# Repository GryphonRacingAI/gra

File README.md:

# Development

## MacOS
On Mac, you may need to run `sudo chown -R $(whoami) ~/.docker` to allow docker to run without sudo.

## X11 auth
To enable X11 forwarding, run `xhost +local:docker` on host computer

## Pre-requisites
- $(hostname).local is broadcasted on the network via mDNS, for both bot and dev computer
- Docker needs to be run on linux

## Notes
- Please make sure the permissions are correct before committing
- To limit Gazebo CPU usage, decrease the update rate in the .world file
    ``` <real_time_update_rate>1000</real_time_update_rate> ```
    e.g. 1000 -> 250

## Known issues
- Ubuntu: memory leak (the memory mysteriously gets full). Deleting the forwarded ports solves the problem some of the time.
- Windows: git on Windows might change the line endings to CRLF which causes a problem when you build the repo. Make sure your line endings are LF if you get the `/bin/sh: 1: /usr/local/bin/apt-get-wrapper.sh: not found` error. `git config --global core.autocrlf false` and recloning the repo should solve the problem. You will need to modify the git config manually if you are using Github desktop and don't have git installed as a command line tool.

## Autonomous System Launch Sequence (full-scale ADS-DV model, with absolute odometry, autocross mission)
1) `roscore`
2) `roslaunch ackermann_vehicle_description ads_dv_sim.launch`
3) `roslaunch ultralytics_ros tracker_with_cloud.launch`
4) `roslaunch ultralytics_ros cone_mapper.launch`
5) `roslaunch fsai_mission autocross.launch`

## Do the following to disable GPU Acceleration: (refer to the wiki page)
1) Go to gra/.devcontainer/docker-compose.yml and comment the deploy section, then rebuild the Docker image in VScode
2) Go to gra/ros/cone_detection/launch/tracker_with_cloud.launch Comment line 17 and uncomment line 15
3) This step reduces Gazebo CPU usage by scaling the simulation time. The simulator will appear slower but CPU load will be reduced significantly.\
Go to gra/ros/ackermann_vehicle_gazebo/worlds/gazebo_world_building/track_small_features.world\
Line 76: <real_time_update_rate>700</real_time_update_rate>\
Reduce the value to reduce CPU load. 1000 is the default value where the simulation time unit = real time unit. When the value is 500, 1 simulation second = 2 real time second.\
Start with 700 and reduce gradually if the cone recognition process is unable to stablise. Unstable process can be observed by the cones swerving in Rviz when the car is steering.

## Commonly used commands
### Basic ROS
- `roscore` to launch ros
- `rosrun {package name} {node name}`
- `roslaunch {package name} {launch file}`
- `rostopic list`
- `rostopic echo {topic name}` print out messages to topic
### Sensors
- `roslaunch rplidar_ros rplidar_a1.launch` to launch the RPlidar
- `roslaunch realsense2_camera rs_aligned_depth.launch` to turn on the Intel depth camera
### Other
- `roslaunch gra_recording record.launch output_name:=recording1 duration:=10s` to record 10s of data
- `rosbag play -l recordings/recording1__timestamp.bag` to play a recording in a loop
- `rosbag record -o {name} --duration=30 /joint_states /rosout /rosout_agg /tf /tf_static /camera/aligned_depth_to_color/camera_info /camera/aligned_depth_to_color/image_raw/compressedDepth /camera/color/camera_info /camera/color/image_raw/compressed` includes the essential topics for recording depth camera rosbags.
- `roslaunch urdf_tutorial display.launch model:=ros/ackermann_vehicle_description/urdf/em_3905_hokuyo.urdf.xacro` to launch RViz with a basic setup (remember the X11 command above)
- `roslaunch gra_recording rviz.launch` to display a recorded stream in RViz
- `rosrun robot_upstart install fsai_api/launch/ads_dv_start.launch --job gra_supervisor_ros --symlink` to make ROS start automatically on boot
- `sudo cp ./driverless_startup.service /etc/systemd/system/driverless_startup.service && sudo systemctl daemon-reload && sudo systemctl enable driverless_startup.service` to register the startup service
- `gsettings set org.gnome.SessionManager logout-prompt false` to disable the 60s shutdown timer on Ubuntu (turn off immediately)

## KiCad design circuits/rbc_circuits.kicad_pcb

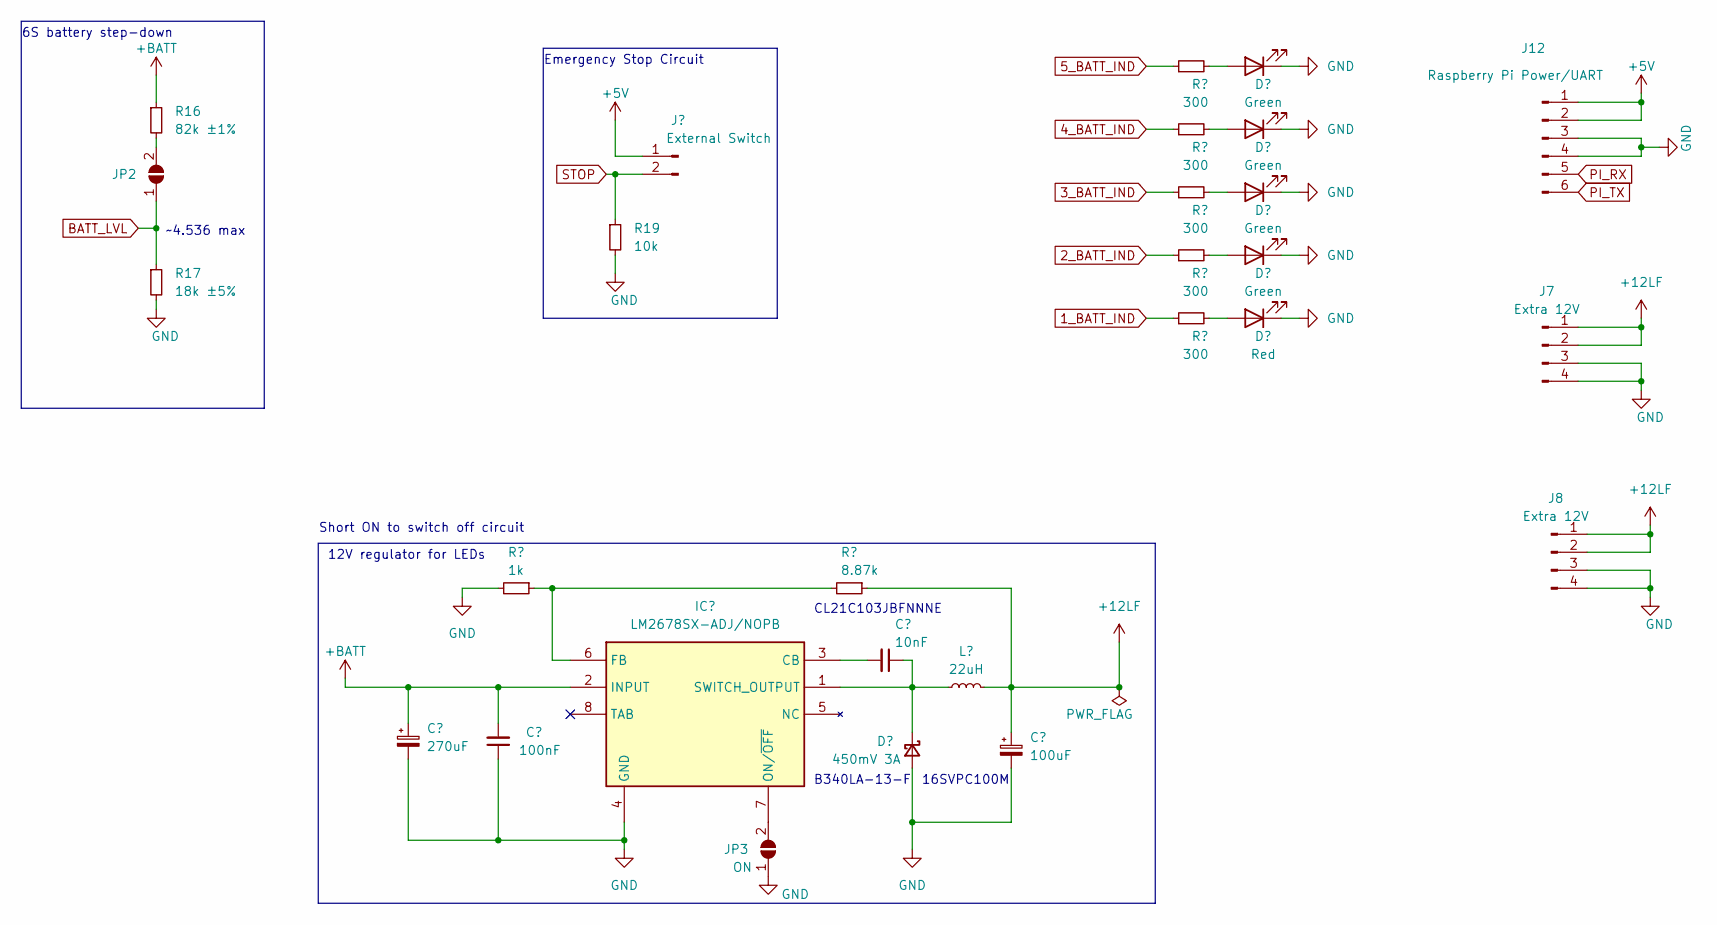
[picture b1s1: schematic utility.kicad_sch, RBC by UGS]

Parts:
C24: 270uF; EEHZS1H221P
C25: 100nF; C_0402_1005Metric
C26: 10nF; C_0805_2012Metric
C27: 100uF; 16SVF180M
D5: 450mV 3A; D_SMA
D6: Green; D_0805_2012Metric; Part No. 17-21/GHC-XS1T2M/3T
D7, D8, D9: Green; D_0805_2012Metric
D10: Red; D_0805_2012Metric; Part No. 17-215/R6C-AQ1R2B/3T
IC5: LM2678SX-ADJ/NOPB; KTW0007B_custom; Mouser Part Number 926-LM2678SX50NOPB
J5: External Switch; TerminalBlock_Phoenix_MKDS-3-2-5.08_1x02_P5.08mm_Horizontal
J7, J8: Extra 12V; Molex_Micro-Fit_3.0_43045-0412_2x02_P3.00mm_Vertical
J12: Raspberry Pi Power/UART; Molex_Micro-Fit_3.0_43045-0612_2x03_P3.00mm_Vertical
JP2: SolderJumper_2_Open; SolderJumper-2_P1.3mm_Open_RoundedPad1.0x1.5mm
JP3: ON; SolderJumper-2_P1.3mm_Open_RoundedPad1.0x1.5mm
L6: 22uH; INDPM110100X400N
R16: 82k ±1%; R_0603_1608Metric_Pad0.98x0.95mm_HandSolder; Part No. RTT038202FTP
R17: 18k ±5%; R_0603_1608Metric_Pad0.98x0.95mm_HandSolder
R18: 1k; R_0201_0603Metric
R19: 10k; R_0402_1005Metric
R20: 8.87k; R_0603_1608Metric
R21, R22, R23, R24, R25: 300; R_0603_1608Metric_Pad0.98x0.95mm_HandSolder

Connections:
1_BATT_IND: R25.1; also elsewhere on the board
2_BATT_IND: R24.1; also elsewhere on the board
3_BATT_IND: R23.1; also elsewhere on the board
4_BATT_IND: R22.1; also elsewhere on the board
5_BATT_IND: R21.1; also elsewhere on the board
+5V: J5.1; also elsewhere on the board
+12LF: C27.1, J7.1, J7.2, J8.1, J8.2, L6.2, R20.1
+BATT: C24.1, C25.2, IC5.2 (INPUT), R16.1; also elsewhere on the board
BATT_LVL: JP2.1 (A), R17.1; also elsewhere on the board
GND: C24.2, C25.1, C27.2, D5.2 (A), D6.1 (K), D7.1 (K), D8.1 (K), D9.1 (K), D10.1 (K), IC5.4 (GND), J7.3, J7.4, J8.3, J8.4, JP3.1 (A), R17.2, R18.2, R19.2; also elsewhere on the board
unnamed: C26.1, D5.1 (K), IC5.1 (SWITCH_OUTPUT), L6.1
unnamed: D6.2 (A), R21.2
unnamed: D7.2 (A), R22.2
unnamed: D8.2 (A), R23.2
unnamed: D9.2 (A), R24.2
unnamed: D10.2 (A), R25.2
unnamed: C26.2, IC5.3 (CB)
unnamed: IC5.6 (FB), R18.1, R20.2
unnamed: IC5.7 (ON/~OFF), JP3.2 (B)
unnamed: JP2.2 (B), R16.2
STOP: J5.2, R19.1; also elsewhere on the board

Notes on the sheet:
~4.536 max
6S battery step-down
16SVPC100M
12V regulator for LEDs
Short ON to switch off circuit
Emergency Stop Circuit
CL21C103JBFNNNE
B340LA-13-F

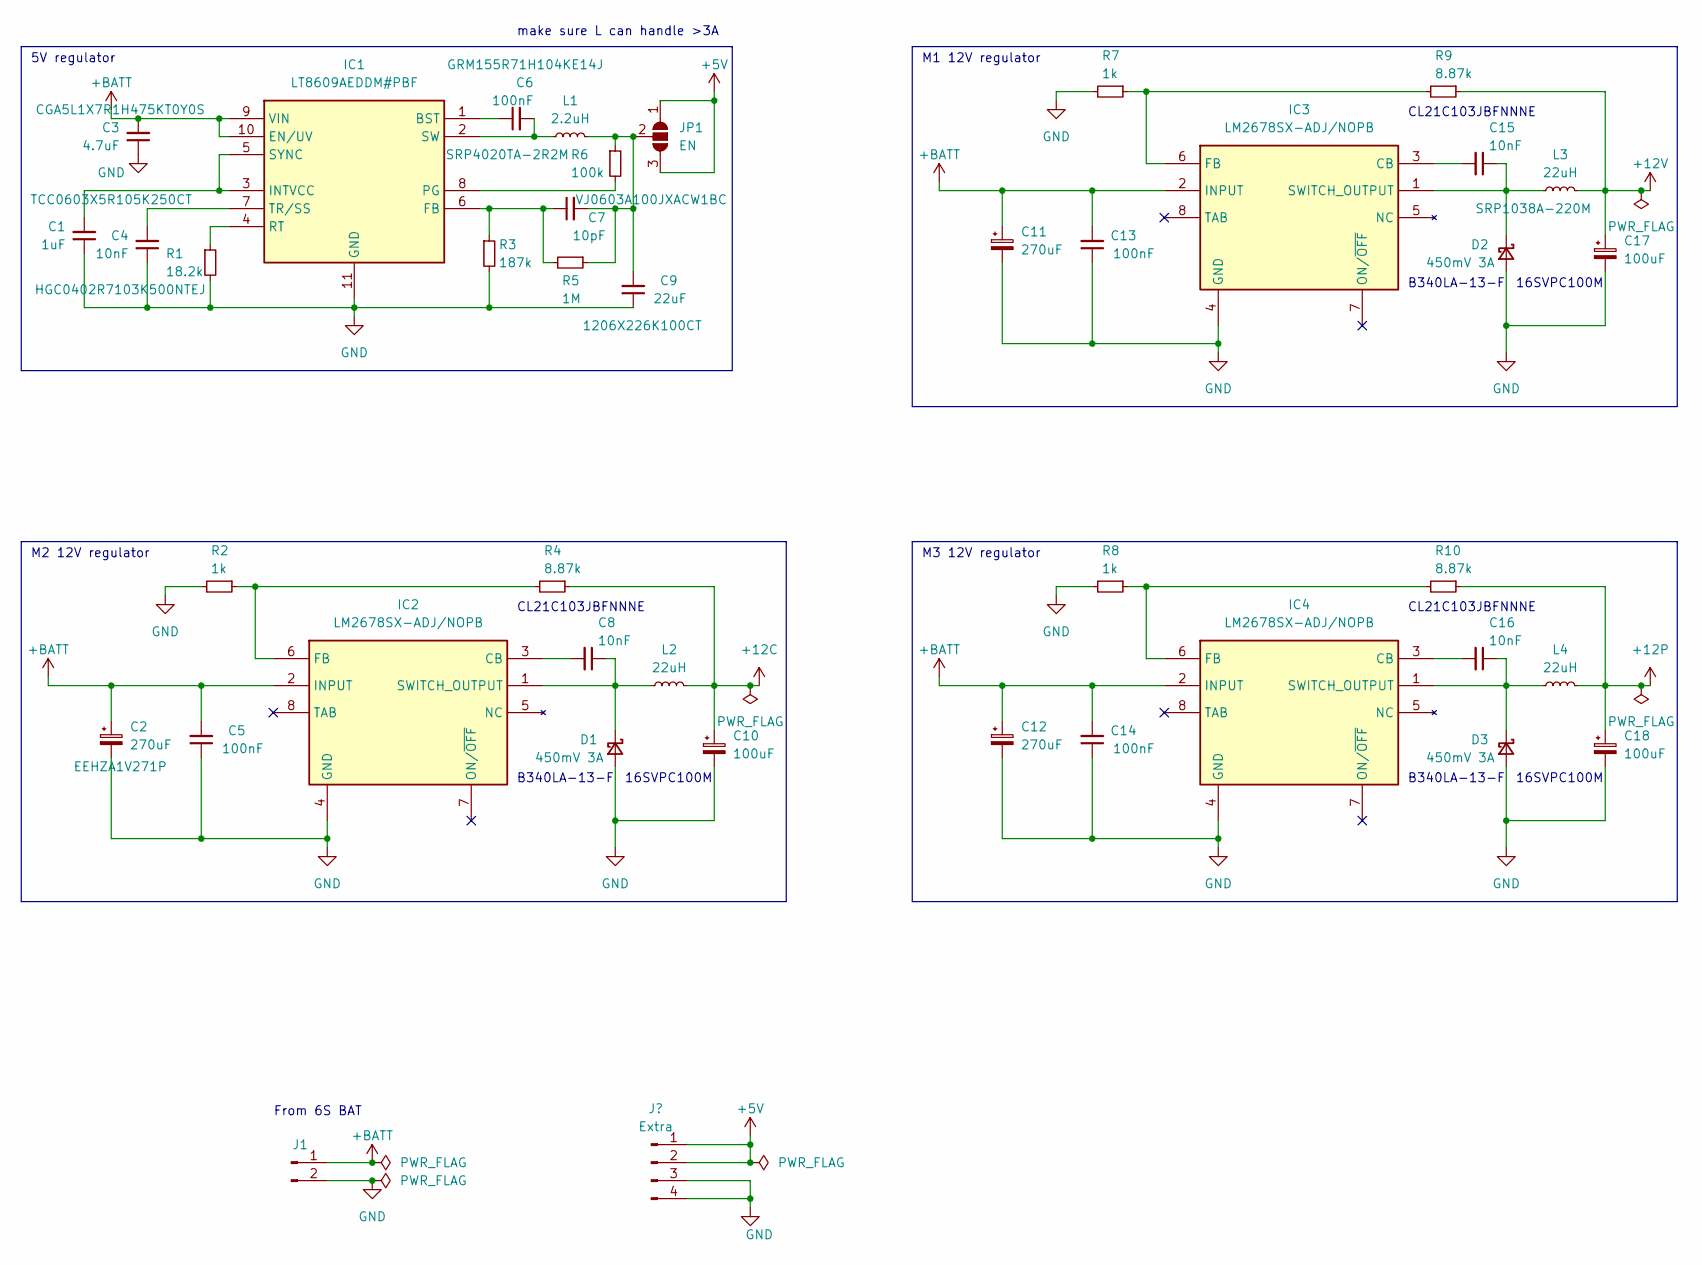
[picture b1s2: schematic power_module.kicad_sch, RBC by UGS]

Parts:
C1: 1uF; C_0603_1608Metric; Part No. TCC0603X5R105K250CT
C2: 270uF; EEHZS1H221P; Part No. EEHZA1V271P
C3: 4.7uF; C_1206_3216Metric; Part No. CGA5L1X7R1H475KT0Y0S
C4: 10nF; C_0402_1005Metric; Part No. HGC0402R7103K500NTEJ
C5, C13, C14: 100nF; C_0402_1005Metric
C6: 100nF; C_0402_1005Metric; Part No. GRM155R71H104KE14J
C7: 10pF; C_0603_1608Metric; Part No. VJ0603A100JXACW1BC
C8, C15, C16: 10nF; C_0805_2012Metric
C9: 22uF; C_1206_3216Metric; Part No. 1206X226K100CT
C10, C17, C18: 100uF; 16SVF180M
C11, C12: 270uF; EEHZS1H221P
D1, D2, D3: 450mV 3A; D_SMA
IC1: LT8609AEDDM#PBF; SON50P300X300X80-11N-D; Mouser Part Number 584-LT8609AEDDM#PBF
IC2, IC3, IC4: LM2678SX-ADJ/NOPB; KTW0007B_custom; Mouser Part Number 926-LM2678SX50NOPB
J1: Conn_01x02_Pin; TerminalBlock_Phoenix_MKDS-3-2-5.08_1x02_P5.08mm_Horizontal
J2: Extra; PinHeader_2x02_P2.54mm_Vertical
JP1: EN; SolderJumper-3_P2.0mm_Open_TrianglePad1.0x1.5mm
L1: 2.2uH; INDC4441X200N; Part No. SRP4020TA-2R2M
L2, L4: 22uH; INDPM110100X400N
L3: 22uH; INDPM110100X400N; Part No. SRP1038A-220M
R1: 18.2k; R_0603_1608Metric_Pad0.98x0.95mm_HandSolder; Part No. CRCW060318K2FKEA
R2: 1k; R_0201_0603Metric; Part No. RC0201FR-071KL
R3: 187k; R_0603_1608Metric; Part No. AC0603FR-07187KL
R4: 8.87k; R_0603_1608Metric; Part No. RT0603BRE078K87L
R5: 1M; R_0402_1005Metric; Part No. AC0402FR-071ML
R6: 100k; R_0201_0603Metric
R7, R8: 1k; R_0201_0603Metric
R9, R10: 8.87k; R_0603_1608Metric

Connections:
+5V: J2.1, J2.2, JP1.1 (A), JP1.3 (B); also elsewhere on the board
+12C: C10.1, L2.2, R4.1; also elsewhere on the board
+12P: C18.1, L4.2, R10.1; also elsewhere on the board
+12V: C17.1, L3.2, R9.1; also elsewhere on the board
+BATT: C2.1, C3.2, C5.2, C11.1, C12.1, C13.2, C14.2, IC1.9 (VIN), IC1.10 (EN/UV), IC2.2 (INPUT), IC3.2 (INPUT), IC4.2 (INPUT), J1.1; also elsewhere on the board
GND: C1.1, C2.2, C3.1, C4.1, C5.1, C9.1, C10.2, C11.2, C12.2, C13.1, C14.1, C17.2, C18.2, D1.2 (A), D2.2 (A), D3.2 (A), IC1.11 (GND), IC2.4 (GND), IC3.4 (GND), IC4.4 (GND), J1.2, J2.3, J2.4, R1.2, R2.2, R3.2, R7.2, R8.2; also elsewhere on the board
unnamed: C8.1, D1.1 (K), IC2.1 (SWITCH_OUTPUT), L2.1
unnamed: C15.1, D2.1 (K), IC3.1 (SWITCH_OUTPUT), L3.1
unnamed: C16.1, D3.1 (K), IC4.1 (SWITCH_OUTPUT), L4.1
unnamed: C6.1, IC1.1 (BST)
unnamed: C7.1, IC1.6 (FB), R3.1, R5.2
unnamed: C1.2, IC1.3 (INTVCC), IC1.5 (SYNC)
unnamed: IC1.8 (PG), R6.2
unnamed: IC1.4 (RT), R1.1
unnamed: C6.2, IC1.2 (SW), L1.1
unnamed: C4.2, IC1.7 (TR/SS)
unnamed: C8.2, IC2.3 (CB)
unnamed: IC2.6 (FB), R2.1, R4.2
unnamed: C15.2, IC3.3 (CB)
unnamed: IC3.6 (FB), R7.1, R9.2
unnamed: C16.2, IC4.3 (CB)
unnamed: IC4.6 (FB), R8.1, R10.2
unnamed: C7.2, C9.2, JP1.2 (C), L1.2, R5.1, R6.1

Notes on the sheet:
CL21C103JBFNNNE
16SVPC100M
B340LA-13-F
make sure L can handle >3A
From 6S BAT
M2 12V regulator
5V regulator
M3 12V regulator
M1 12V regulator

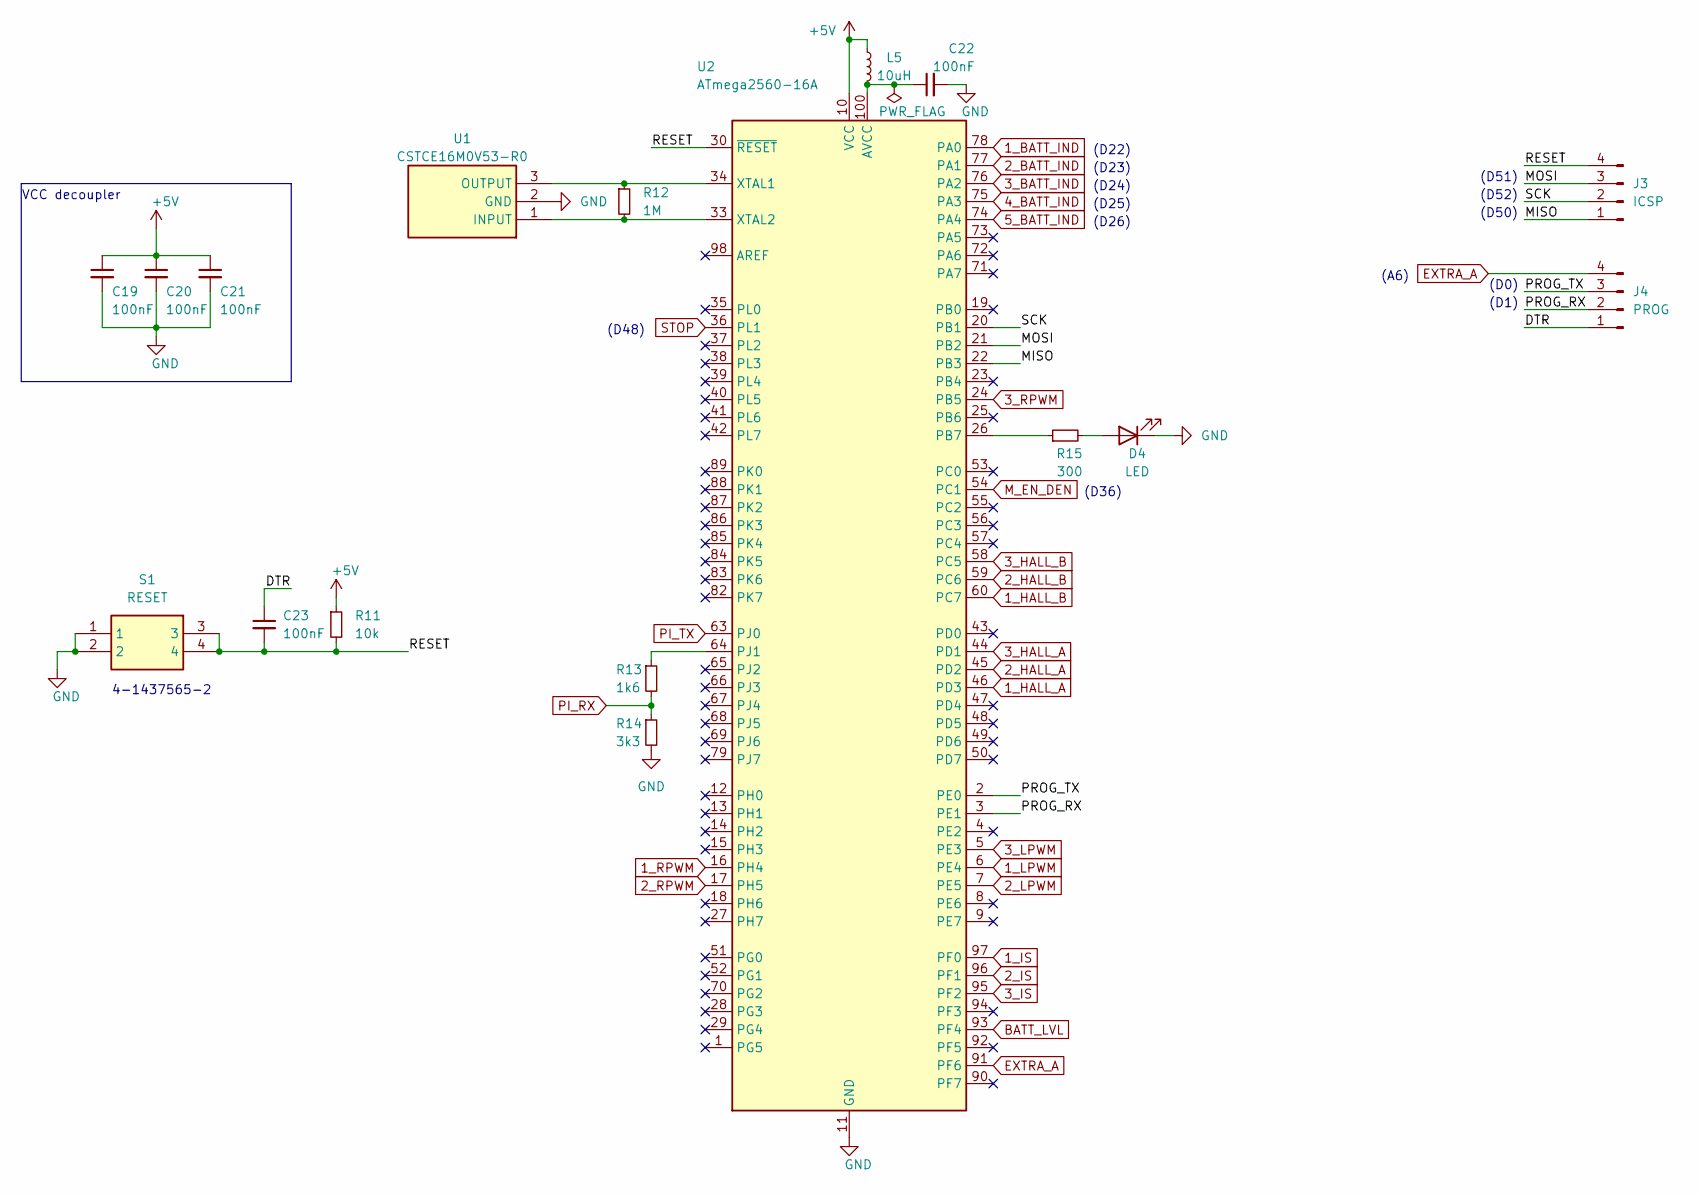
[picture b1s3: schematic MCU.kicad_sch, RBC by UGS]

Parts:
C19, C20, C21, C22, C23: 100nF; C_0402_1005Metric
D4: LED; D_0805_2012Metric; Part No. NCD0805Y1
J3: ICSP; PinHeader_2x02_P2.54mm_Vertical
J4: PROG; PinHeader_2x02_P2.54mm_Vertical
L5: 10uH; L_0805_2012Metric; Part No. MLZ2012M100HT000
R11: 10k; R_0402_1005Metric; Part No. AC0402FR-0710KL
R12: 1M; R_0402_1005Metric
R13: 1k6; R_0805_2012Metric_Pad1.20x1.40mm_HandSolder
R14: 3k3; R_1206_3216Metric_Pad1.30x1.75mm_HandSolder
R15: 300; R_0603_1608Metric_Pad0.98x0.95mm_HandSolder; Part No. CR0603-FX-3000ELF
S1: RESET; FSM4JSMATR; Mouser Part Number 506-FSM4JSMATR
U1: CSTCE16M0V53-R0; CSTCE16M0V53R0; Mouser Part Number 81-CSTNE16M0V530000R
U2: ATmega2560-16A; TQFP-100_14x14mm_P0.5mm

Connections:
1_BATT_IND: U2.78 (PA0); also elsewhere on the board
1_HALL_A: U2.46 (PD3); also elsewhere on the board
1_HALL_B: U2.60 (PC7); also elsewhere on the board
1_IS: U2.97 (PF0); also elsewhere on the board
1_LPWM: U2.6 (PE4); also elsewhere on the board
1_RPWM: U2.16 (PH4); also elsewhere on the board
2_BATT_IND: U2.77 (PA1); also elsewhere on the board
2_HALL_A: U2.45 (PD2); also elsewhere on the board
2_HALL_B: U2.59 (PC6); also elsewhere on the board
2_IS: U2.96 (PF1); also elsewhere on the board
2_LPWM: U2.7 (PE5); also elsewhere on the board
2_RPWM: U2.17 (PH5); also elsewhere on the board
3_BATT_IND: U2.76 (PA2); also elsewhere on the board
3_HALL_A: U2.44 (PD1); also elsewhere on the board
3_HALL_B: U2.58 (PC5); also elsewhere on the board
3_IS: U2.95 (PF2); also elsewhere on the board
3_LPWM: U2.5 (PE3); also elsewhere on the board
3_RPWM: U2.24 (PB5); also elsewhere on the board
4_BATT_IND: U2.75 (PA3); also elsewhere on the board
5_BATT_IND: U2.74 (PA4); also elsewhere on the board
+5V: C19.1, C20.1, C21.1, L5.1, R11.1, U2.10 (VCC), U2.31 (VCC), U2.61 (VCC), U2.80 (VCC); also elsewhere on the board
/MCU/DTR: C23.1, J4.1
/MCU/MISO: J3.1, U2.22 (PB3)
/MCU/MOSI: J3.3, U2.21 (PB2)
/MCU/PROG_RX: J4.2, U2.3 (PE1)
/MCU/PROG_TX: J4.3, U2.2 (PE0)
/MCU/RESET: C23.2, J3.4, R11.2, S1.3, S1.4, U2.30 (~RESET)
/MCU/SCK: J3.2, U2.20 (PB1)
BATT_LVL: U2.93 (PF4); also elsewhere on the board
EXTRA_A: J4.4, U2.91 (PF6)
GND: C19.2, C20.2, C21.2, C22.2, D4.1 (K), R14.2, S1.1, S1.2, U1.2 (GND), U2.11 (GND), U2.32 (GND), U2.62 (GND), U2.81 (GND), U2.99 (GND); also elsewhere on the board
M_EN_DEN: U2.54 (PC1); also elsewhere on the board
unnamed: D4.2 (A), R15.2
unnamed: R12.2, U1.1 (INPUT), U2.33 (XTAL2)
unnamed: R12.1, U1.3 (OUTPUT), U2.34 (XTAL1)
unnamed: C22.1, L5.2, U2.100 (AVCC)
unnamed: R15.1, U2.26 (PB7)
unnamed: R13.1, U2.64 (PJ1)
PI_RX: R13.2, R14.1; also elsewhere on the board
PI_TX: U2.63 (PJ0); also elsewhere on the board
STOP: U2.36 (PL1); also elsewhere on the board

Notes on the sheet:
(D52)
(D22)
(D23)
(D36)
(D25)
(D26)
(D51)
(D48)
VCC decoupler
(D0)
(D1)
(D50)
(A6)
4-1437565-2
(D24)

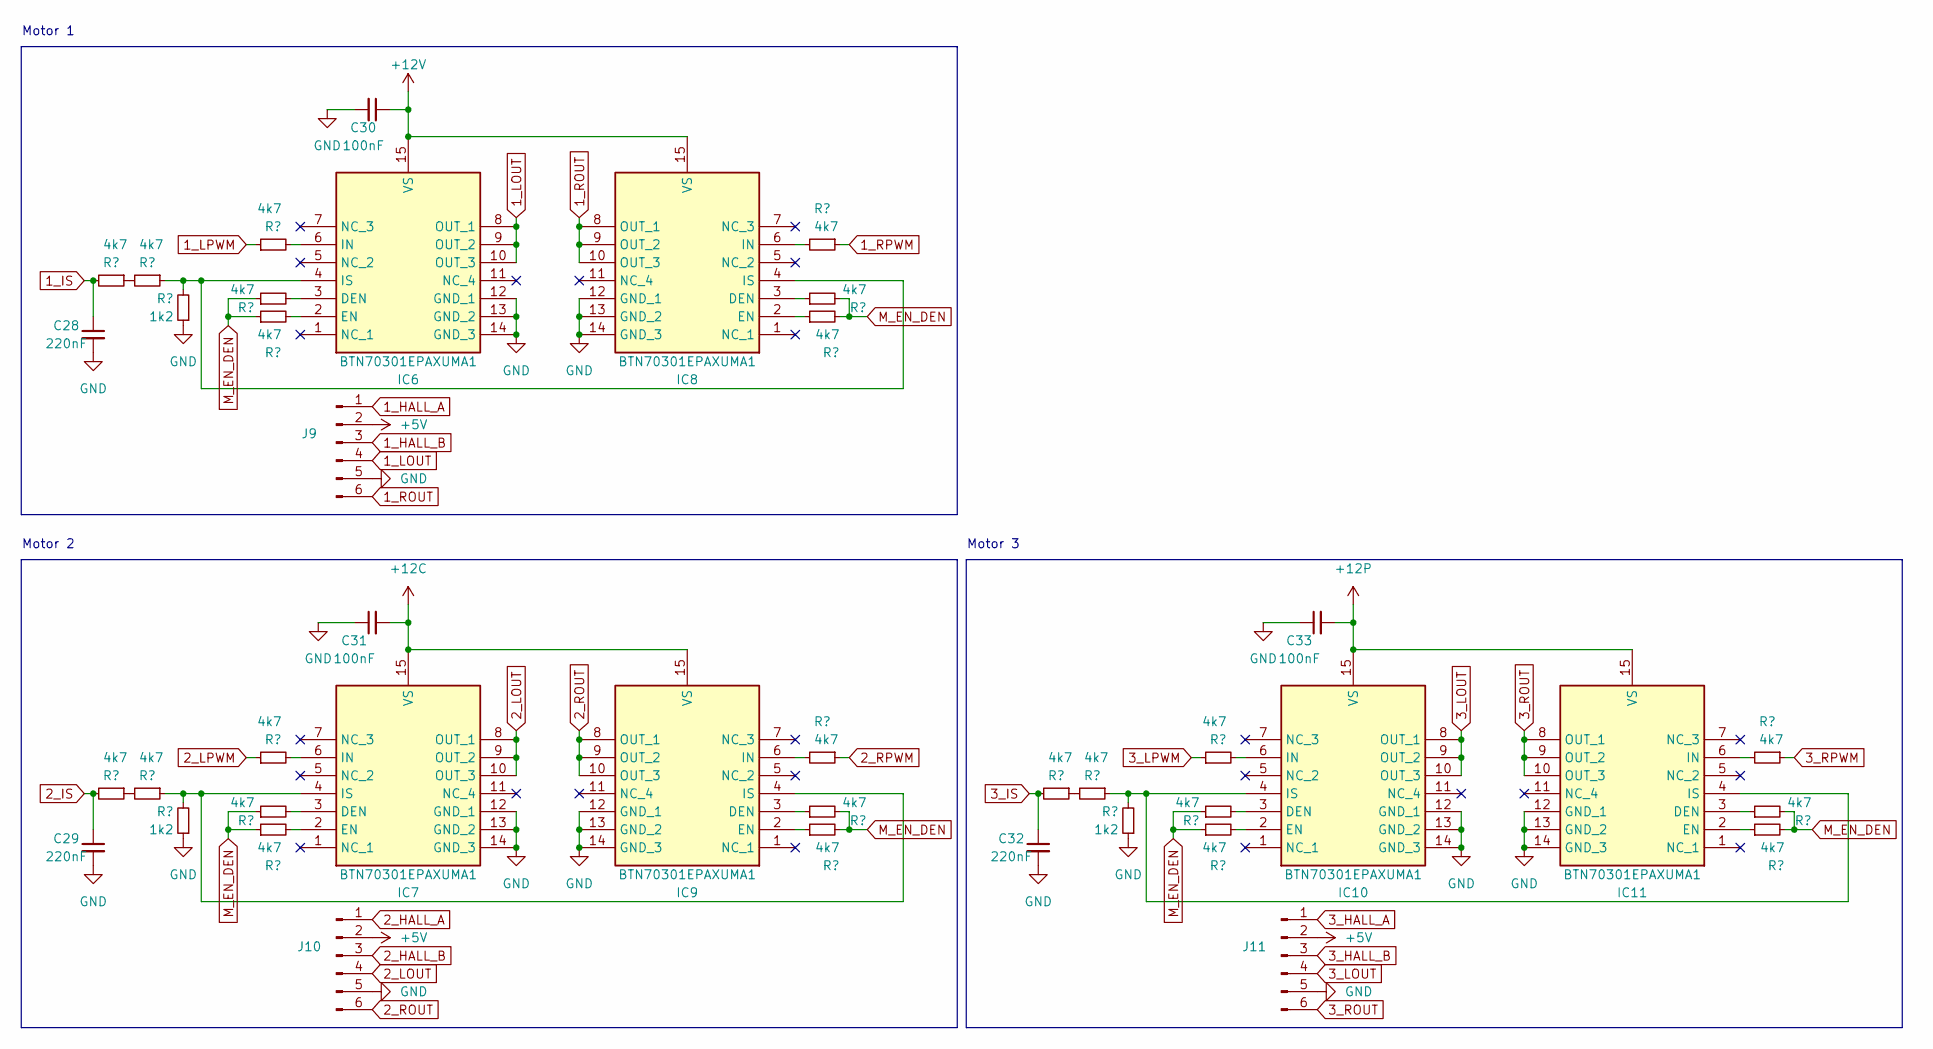
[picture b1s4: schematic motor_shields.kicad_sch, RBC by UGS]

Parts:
C28, C29, C32: 220nF; C_0805_2012Metric
C30, C31, C33: 100nF; C_0402_1005Metric
IC6, IC7, IC8, IC9, IC10, IC11: BTN70301EPAXUMA1; Infineon_PG-TSDSO-14-22_custom; Mouser Part Number 726-BTN70301EPAXUMA1
J9, J10, J11: Conn_01x06_Pin; Molex_Micro-Fit_3.0_43045-0612_2x03_P3.00mm_Vertical
R26, R27, R28, R29, R32, R33, R34, R35, R36, R37, R38, R39, R40, R41, R42, R43, R44, R45, R47, R48, R49, R50, R51, R52: 4k7; R_1206_3216Metric
R30, R31, R46: 1k2; R_1206_3216Metric

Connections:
1_HALL_A: J9.1; also elsewhere on the board
1_HALL_B: J9.3; also elsewhere on the board
1_IS: C28.1, R26.2; also elsewhere on the board
1_LOUT: IC6.8 (OUT_1), IC6.9 (OUT_2), IC6.10 (OUT_3), J9.4
1_LPWM: R32.1; also elsewhere on the board
1_ROUT: IC8.8 (OUT_1), IC8.9 (OUT_2), IC8.10 (OUT_3), J9.6
1_RPWM: R38.1; also elsewhere on the board
2_HALL_A: J10.1; also elsewhere on the board
2_HALL_B: J10.3; also elsewhere on the board
2_IS: C29.1, R27.2; also elsewhere on the board
2_LOUT: IC7.8 (OUT_1), IC7.9 (OUT_2), IC7.10 (OUT_3), J10.4
2_LPWM: R35.1; also elsewhere on the board
2_ROUT: IC9.8 (OUT_1), IC9.9 (OUT_2), IC9.10 (OUT_3), J10.6
2_RPWM: R41.1; also elsewhere on the board
3_HALL_A: J11.1; also elsewhere on the board
3_HALL_B: J11.3; also elsewhere on the board
3_IS: C32.1, R44.2; also elsewhere on the board
3_LOUT: IC10.8 (OUT_1), IC10.9 (OUT_2), IC10.10 (OUT_3), J11.4
3_LPWM: R47.1; also elsewhere on the board
3_ROUT: IC11.8 (OUT_1), IC11.9 (OUT_2), IC11.10 (OUT_3), J11.6
3_RPWM: R50.1; also elsewhere on the board
+5V: J9.2, J10.2, J11.2; also elsewhere on the board
+12C: C31.2, IC7.15 (VS), IC9.15 (VS); also elsewhere on the board
+12P: C33.2, IC10.15 (VS), IC11.15 (VS); also elsewhere on the board
+12V: C30.1, IC6.15 (VS), IC8.15 (VS); also elsewhere on the board
GND: C28.2, C29.2, C30.2, C31.1, C32.2, C33.1, IC6.12 (GND_1), IC6.13 (GND_2), IC6.14 (GND_3), IC7.12 (GND_1), IC7.13 (GND_2), IC7.14 (GND_3), IC8.12 (GND_1), IC8.13 (GND_2), IC8.14 (GND_3), IC9.12 (GND_1), IC9.13 (GND_2), IC9.14 (GND_3), IC10.12 (GND_1), IC10.13 (GND_2), IC10.14 (GND_3), IC11.12 (GND_1), IC11.13 (GND_2), IC11.14 (GND_3), J9.5, J10.5, J11.5, R30.1, R31.1, R46.1; also elsewhere on the board
M_EN_DEN: R33.1, R34.1, R36.1, R37.1, R39.2, R40.2, R42.2, R43.2, R48.1, R49.1, R51.2, R52.2; also elsewhere on the board
unnamed: IC6.3 (DEN), R33.2
unnamed: IC6.2 (EN), R34.2
unnamed: IC6.6 (IN), R32.2
unnamed: IC6.4 (IS), IC8.4 (IS), R28.1, R30.2
unnamed: IC7.3 (DEN), R36.2
unnamed: IC7.2 (EN), R37.2
unnamed: IC7.6 (IN), R35.2
unnamed: IC7.4 (IS), IC9.4 (IS), R29.1, R31.2
unnamed: IC8.3 (DEN), R39.1
unnamed: IC8.2 (EN), R40.1
unnamed: IC8.6 (IN), R38.2
unnamed: IC9.3 (DEN), R42.1
unnamed: IC9.2 (EN), R43.1
unnamed: IC9.6 (IN), R41.2
unnamed: IC10.3 (DEN), R48.2
unnamed: IC10.2 (EN), R49.2
unnamed: IC10.6 (IN), R47.2
unnamed: IC10.4 (IS), IC11.4 (IS), R45.1, R46.2
unnamed: IC11.3 (DEN), R51.1
unnamed: IC11.2 (EN), R52.1
unnamed: IC11.6 (IN), R50.2
unnamed: R26.1, R28.2
unnamed: R27.1, R29.2
unnamed: R44.1, R45.2

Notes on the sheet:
Motor 2
Motor 3
Motor 1

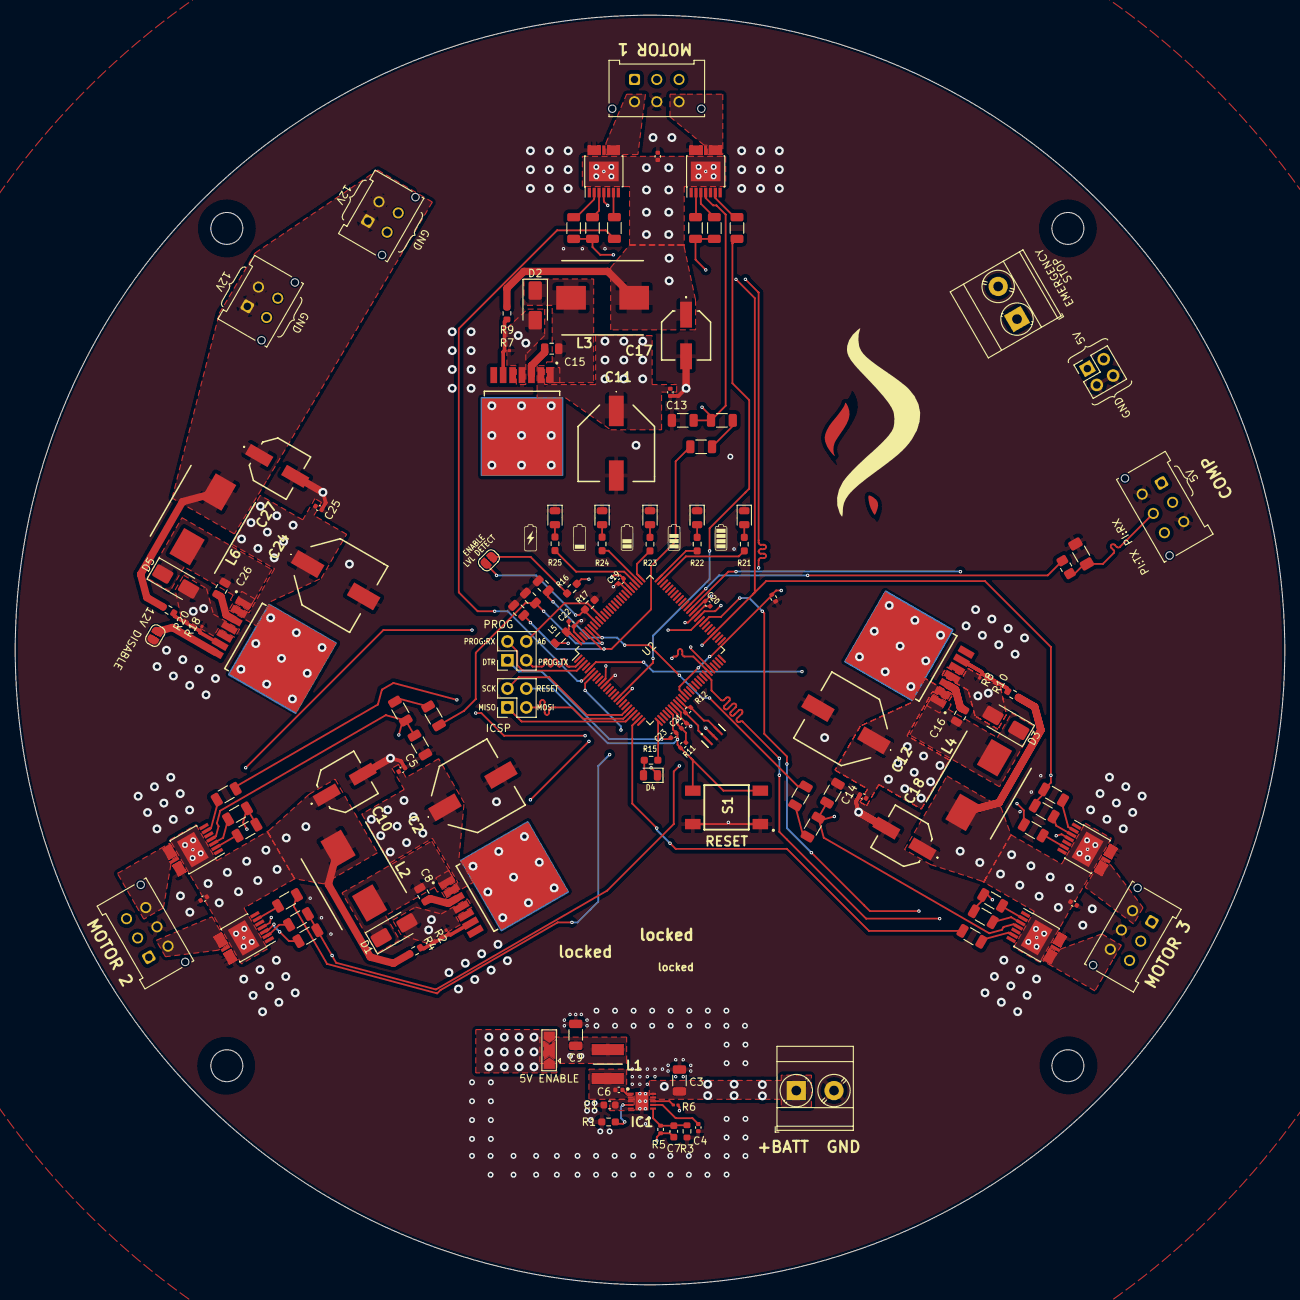
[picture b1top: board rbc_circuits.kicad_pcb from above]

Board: 4 copper layers, 171.0 x 171.0 mm, 129 parts (0 on the bottom side), 103 nets.

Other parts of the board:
J6: Raspberry Pi Power/UART; Molex_Micro-Fit_3.0_43045-0612_2x03_P3.00mm_Vertical

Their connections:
+5V: J6.1, J6.2; also elsewhere on the board
GND: J6.3, J6.4; also elsewhere on the board
PI_RX: J6.5; also elsewhere on the board
PI_TX: J6.6; also elsewhere on the board

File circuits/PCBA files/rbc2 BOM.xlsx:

Comment | Designator | Footprint | JLCPCB Part #
1uF | C1 | Capacitor_SMD:C_0603_1608Metric | C696843
270uF | C2, C11, C12, C24 | EEHZS1H221P | C79124
4.7uF | C3 | Capacitor_SMD:C_1206_3216Metric | C412300
10nF | C4 | Capacitor_SMD:C_0402_1005Metric | C482489
100nF | C5, C6, C13, C14, C19, C20, C21, C22, C23, C25, C30, C31, C33 | Capacitor_SMD:C_0402_1005Metric | C2649519
10pF | C7 | Capacitor_SMD:C_0603_1608Metric | C2171298
10nF | C8, C15, C16, C26 | Capacitor_SMD:C_0805_2012Metric | C27071
22uF | C9 | Capacitor_SMD:C_1206_3216Metric | C304004
100uF | C10, C17, C18, C27 | 16SVF180M | C136275
220nF | C28, C29, C32 | Capacitor_SMD:C_0805_2012Metric | C913663
450mV 3A Schottky Diode | D1, D2, D3, D5 | Diode_SMD:D_SMA | C17101
Yellow LED | D4 | Diode_SMD:D_0805_2012Metric | C84261
Green LED | D6, D7, D8, D9 | Diode_SMD:D_0805_2012Metric | C63855
Red LED | D10 | Diode_SMD:D_0805_2012Metric | C86865
LT8609AEDDM#PBF | IC1 | SON50P300X300X80-11N-D | C673976
LM2678SX-ADJ/NOPB | IC2, IC3, IC4, IC5 | KTW0007B | C40844
BTN70301EPAXUMA1 | IC6, IC7, IC8, IC9, IC10, IC11 | Infineon_PG-TSDSO-14-22 | C3655686
DNP | J1 | TerminalBlock_Phoenix:TerminalBlock_Phoenix_MKDS-3-2-5.08_1x02_P5.08mm_Horizont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
DNP | J2 | Connector_PinHeader_2.54mm:PinHeader_2x02_P2.54mm_Vertical
DNP | J3 | Connector_PinHeader_2.54mm:PinHeader_2x02_P2.54mm_Vertical
DNP | J4 | Connector_PinHeader_2.54mm:PinHeader_2x02_P2.54mm_Vertical
DNP | J5 | TerminalBlock_Phoenix:TerminalBlock_Phoenix_MKDS-3-2-5.08_1x02_P5.08mm_Horizont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
DNP | J6 | Connector_Molex:Molex_Micro-Fit_3.0_43045-0612_2x03_P3.00mm_Vertical
DNP | J7, J8 | Connector_Molex:Molex_Micro-Fit_3.0_43045-0412_2x02_P3.00mm_Vertical
DNP | J9, J10, J11 | Connector_Molex:Molex_Micro-Fit_3.0_43045-0612_2x03_P3.00mm_Vertical
2.2uH | L1 | INDC4441X200N | C719179
22uH | L2, L3, L4, L6 | INDPM110100X400N | C2047201
10uH | L5 | Inductor_SMD:L_0805_2012Metric | C88172
18.2k | R1 | Resistor_SMD:R_0603_1608Metric_Pad0.98x0.95mm_HandSolder | C844532
1k | R2, R7, R8, R18 | Resistor_SMD:R_0201_0603Metric | C138165
187k | R3 | Resistor_SMD:R_0603_1608Metric | C227629
8.87k | R4, R9, R10, R20 | Resistor_SMD:R_0603_1608Metric | C862310
1M | R5, R12 | Resistor_SMD:R_0402_1005Metric | C144787
100k | R6 | Resistor_SMD:R_0201_0603Metric | C100127
10k | R11, R19 | Resistor_SMD:R_0402_1005Metric | C144807
1.6k | R13 | Resistor_SMD:R_0805_2012Metric_Pad1.20x1.40mm_HandSolder | C316776
3.3k | R14 | Resistor_SMD:R_1206_3216Metric_Pad1.30x1.75mm_HandSolder | C104771
300 | R15, R21, R22, R23, R24, R25 | Resistor_SMD:R_0603_1608Metric_Pad0.98x0.95mm_HandSolder | C203500
82k ±1% | R16 | Resistor_SMD:R_0603_1608Metric_Pad0.98x0.95mm_HandSolder | C103831
18k ±5% | R17 | Resistor_SMD:R_0603_1608Metric_Pad0.98x0.95mm_HandSolder | C445839
4.7k | R26, R27, R28, R29, R32, R33, R34, R35, R36, R37, R38, R39, R40, R41, R42, R43,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 | Resistor_SMD:R_1206_3216Metric | C432834
1.2k | R30, R31, R46 | Resistor_SMD:R_1206_3216Metric | C340507
RESET Switch | S1 | FSM4JSMATR | C86487
CSTCE16M0V53-R0 | U1 | CSTCE16M0V53R0 | C32180
ATmega2560-16A | U2 | Package_QFP:TQFP-100_14x14mm_P0.5mm | C22460

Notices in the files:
circuits/rbc_circuits.kicad_pcb:
© UGS 2023
